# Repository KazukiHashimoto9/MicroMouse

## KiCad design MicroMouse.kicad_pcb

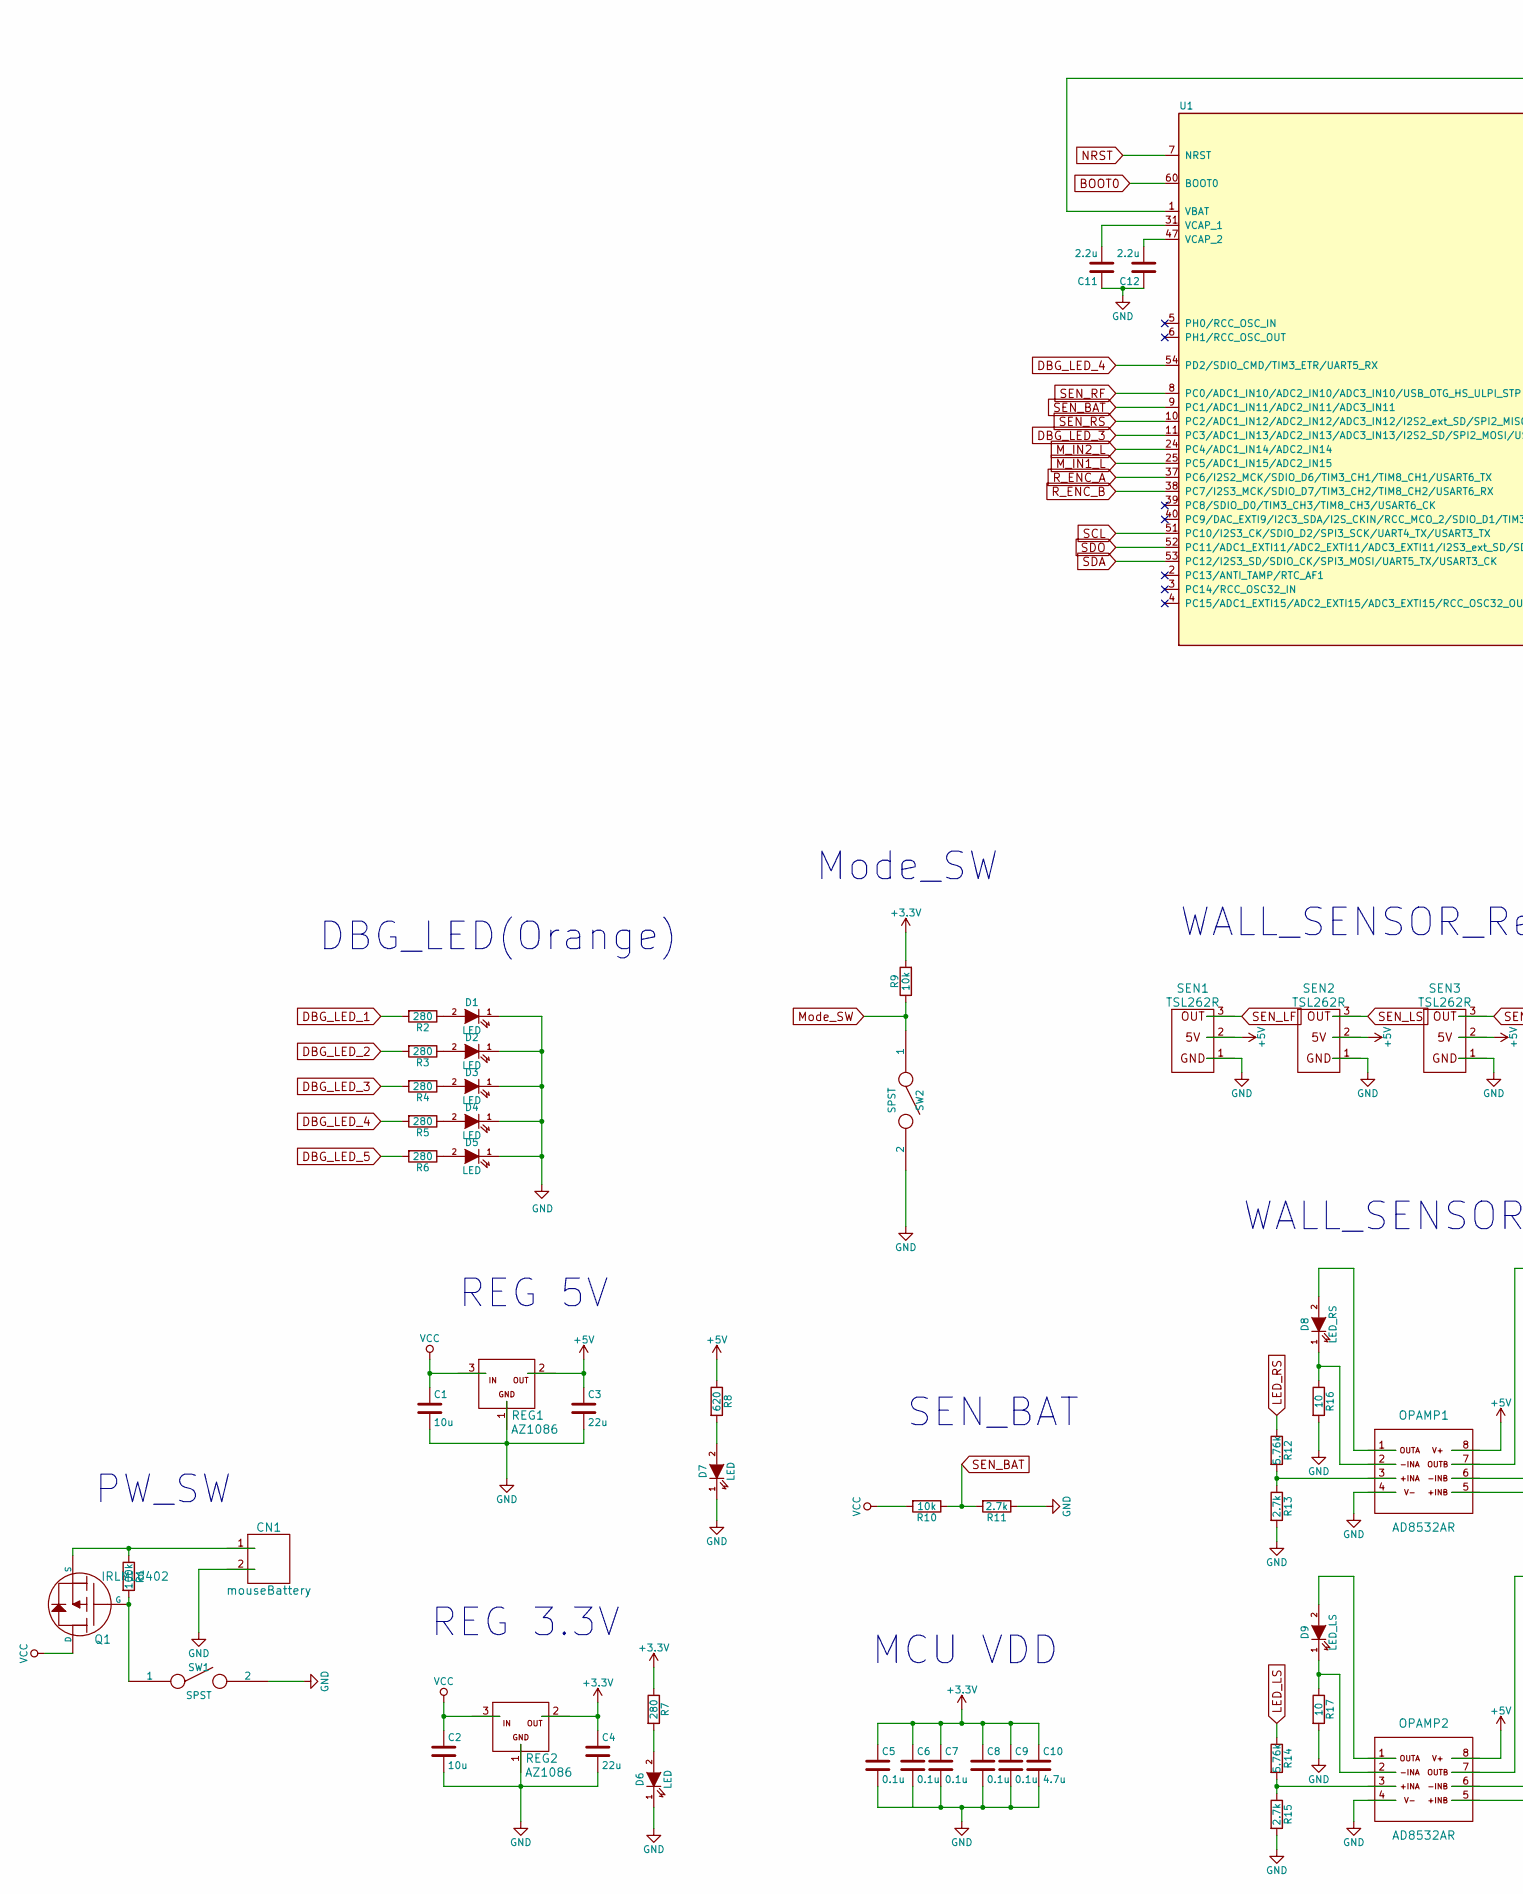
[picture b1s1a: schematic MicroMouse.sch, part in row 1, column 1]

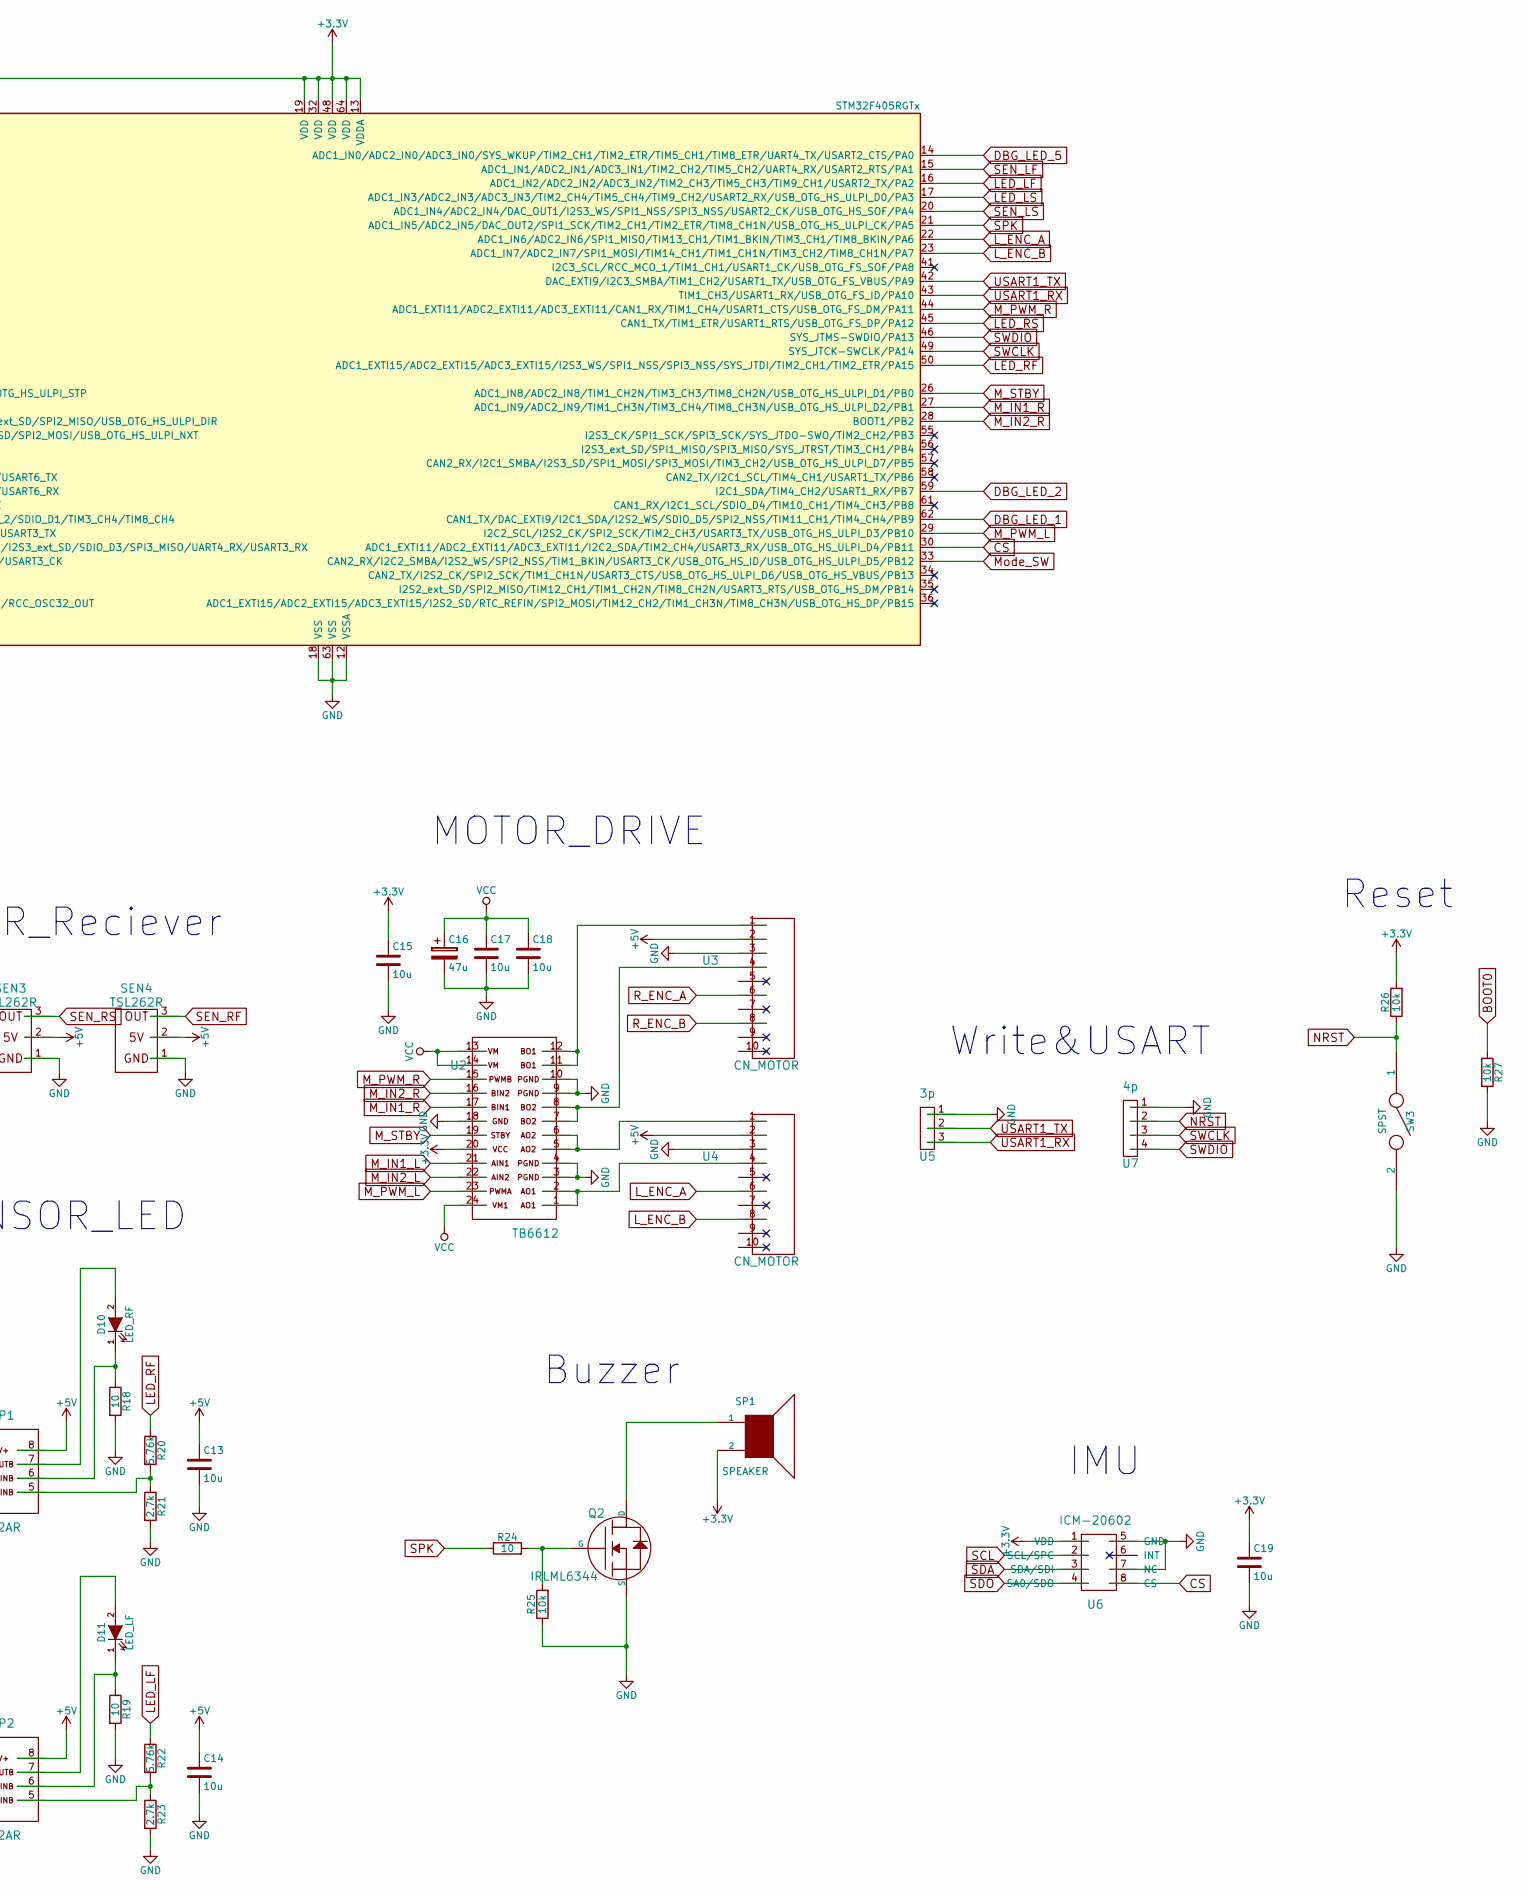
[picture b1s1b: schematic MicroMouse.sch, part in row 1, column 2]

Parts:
C1, C2, C13, C14, C15, C17, C18, C19: 10u; R_0603_HandSoldering
C3, C4: 22u; R_0603_HandSoldering
C5, C6, C7, C8, C9: 0.1u; R_0603_HandSoldering
C10: 4.7u; R_0603_HandSoldering
C11, C12: 2.2u; R_0603_HandSoldering
C16: 47u; c_elec_6.3x7.7
CN1: mouseBattery; XA_2T
D1, D2, D3, D4, D5, D6, D7: LED; R_0603_HandSoldering
D8: LED_RS; LED-5MM
D9: LED_LS; LED-5MM
D10: LED_RF; LED-5MM
D11: LED_LF; LED-5MM
OPAMP1, OPAMP2: AD8532AR; SOIC-8_3.9x4.9mm_Pitch1.27mm
Q1: IRLML6402; SOT-23_Handsoldering
Q2: IRLML6344; SOT-23_Handsoldering
R1: 100k; R_0603_HandSoldering
R2, R3, R4, R5, R6, R7: 280; R_0603_HandSoldering
R8: 620; R_0603_HandSoldering
R9, R10, R25, R26, R27: 10k; R_0603_HandSoldering
R11, R13, R15, R21, R23: 2.7k; R_0603_HandSoldering
R12, R14, R20, R22: 5.76k; R_0603_HandSoldering
R16, R17, R18, R19, R24: 10; R_0603_HandSoldering
REG1, REG2: AZ1086; SOT-223_reg
SEN1, SEN2, SEN3, SEN4: TSL262R; Socket_Strip_Straight_1x03
SP1: SPEAKER; CSS-0575A-SMT
SW1: SPST; SS12D01G4
SW2, SW3: SPST; TVBP06-BN043CB-B
U1: STM32F405RGTx; LQFP-64_10x10mm_Pitch0.5mm
U2: TB6612; SSOP-24_5.3x8.2mm_Pitch0.65mm
U3, U4: CN_MOTOR; BH-10SG
U5: 3p; Pin_Header_Straight_1x03
U6: ICM-20602
U7: 4p; Pin_Header_Straight_1x04

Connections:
+3V3: C4.1, C5.1, C6.1, C7.1, C8.1, C9.1, C10.1, C15.1, C19.1, R7.1, R9.2, R26.2, REG2.2, SP1.2, U1.1 (VBAT), U1.13 (VDDA), U1.19 (VDD), U1.32 (VDD), U1.48 (VDD), U1.64 (VDD), U2.20, U6.1 (VDD); also elsewhere on the board
+5V: C3.1, C13.1, C14.1, OPAMP1.8, OPAMP2.8, R8.1, REG1.2, SEN1.2, SEN2.2, SEN3.2, SEN4.2, U3.2, U4.2; also elsewhere on the board
BOOT0: R27.1, U1.60 (BOOT0)
CS: U1.30 (ADC1_EXTI11/ADC2_EXTI11/ADC3_EXTI11/I2C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), U6.8 (CS)
DBG_LED_1: R2.2, U1.62 (CAN1_TX/DAC_EXTI9/I2C1_SDA/I2S2_WS/SDIO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)
DBG_LED_2: R3.2, U1.59 (I2C1_SDA/TIM4_CH2/USART1_RX/PB7)
DBG_LED_3: R4.2, U1.11 (PC3/ADC1_IN13/ADC2_IN13/ADC3_IN13/I2S2_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)
DBG_LED_4: R5.2, U1.54 (PD2/SDIO_CMD/TIM3_ETR/UART5_RX)
DBG_LED_5: R6.2, U1.14 (ADC1_IN0/ADC2_IN0/ADC3_IN0/SYS_WKUP/TIM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)
GND: C1.2, C2.2, C3.2, C4.2, C5.2, C7.2, C8.2, C9.2, C10.2, C11.1, C12.1, C13.2, C14.2, C15.2, C16.2, C17.2, C18.2, C19.2, CN1.2, D1.1 (K), D2.1 (K), D3.1 (K), D4.1 (K), D5.1 (K), D6.1 (K), D7.1 (K), OPAMP1.4, OPAMP2.4, Q2.2 (S), R11.1, R13.2, R15.2, R16.2, R17.2, R18.2, R19.2, R21.2, R23.2, R25.1, R27.2, REG1.1, REG2.1, SEN1.1, SEN2.1, SEN3.1, SEN4.1, SW1.2, SW2.2, SW3.2, U1.12 (VSSA), U1.18 (VSS), U1.63 (VSS), U2.3, U2.4, U2.9, U2.10, U2.18, U3.3, U4.3, U5.1, U6.5 (GND), U6.7 (NC), U7.1; also elsewhere on the board
LED_LF: R22.1, U1.16 (ADC1_IN2/ADC2_IN2/ADC3_IN2/TIM2_CH3/TIM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)
LED_LS: R14.1, U1.17 (ADC1_IN3/ADC2_IN3/ADC3_IN3/TIM2_CH4/TIM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)
LED_RF: R20.1, U1.50 (ADC1_EXTI15/ADC2_EXTI15/ADC3_EXTI15/I2S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)
LED_RS: R12.1, U1.45 (CAN1_TX/TIM1_ETR/USART1_RTS/USB_OTG_FS_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)
L_ENC_A: U1.22 (ADC1_IN6/ADC2_IN6/SPI1_MISO/TIM13_CH1/T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), U4.6
L_ENC_B: U1.23 (ADC1_IN7/ADC2_IN7/SPI1_MOSI/TIM14_CH1/T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), U4.8
M_IN1_L: U1.25 (PC5/ADC1_IN15/ADC2_IN15), U2.21
M_IN1_R: U1.27 (ADC1_IN9/ADC2_IN9/TIM1_CH3N/TIM3_CH4/TI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), U2.17
M_IN2_L: U1.24 (PC4/ADC1_IN14/ADC2_IN14), U2.22
M_IN2_R: U1.28 (BOOT1/PB2), U2.16
M_PWM_L: U1.29 (I2C2_SCL/I2S2_CK/SPI2_SCK/TIM2_CH3/USAR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), U2.23
M_PWM_R: U1.44 (ADC1_EXTI11/ADC2_EXTI11/ADC3_EXTI11/CAN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), U2.15
M_STBY: U1.26 (ADC1_IN8/ADC2_IN8/TIM1_CH2N/TIM3_CH3/TI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), U2.19
Mode_SW: R9.1, SW2.1, U1.33 (CAN2_RX/I2C2_SMBA/I2S2_WS/SPI2_NSS/TIM1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); also elsewhere on the board
NRST: R26.1, SW3.1, U1.7 (NRST), U7.2; also elsewhere on the board
unnamed: C11.2, U1.31 (VCAP_1)
unnamed: C12.2, U1.47 (VCAP_2)
unnamed: CN1.1, Q1.2 (S), R1.1
unnamed: D1.2 (A), R2.1
unnamed: D2.2 (A), R3.1
unnamed: D3.2 (A), R4.1
unnamed: D4.2 (A), R5.1
unnamed: D5.2 (A), R6.1
unnamed: D6.2 (A), R7.2
unnamed: D7.2 (A), R8.2
unnamed: D8.1 (K), OPAMP1.2, R16.1
unnamed: D8.2 (A), OPAMP1.1
unnamed: D9.1 (K), OPAMP2.2, R17.1
unnamed: D9.2 (A), OPAMP2.1
unnamed: D10.1 (K), OPAMP1.6, R18.1
unnamed: D10.2 (A), OPAMP1.7
unnamed: D11.1 (K), OPAMP2.6, R19.1
unnamed: D11.2 (A), OPAMP2.7
unnamed: OPAMP1.3, R12.2, R13.1
unnamed: OPAMP1.5, R20.2, R21.1
unnamed: OPAMP2.3, R14.2, R15.1
unnamed: OPAMP2.5, R22.2, R23.1
unnamed 47: Q1.1 (G), R1.2, SW1.1; also elsewhere on the board
unnamed: Q2.1 (G), R24.2, R25.2
unnamed 49: Q2.3 (D), SP1.1; also elsewhere on the board
unnamed: U2.1, U2.2, U4.4
unnamed: U2.5, U2.6, U4.1
unnamed: U2.7, U2.8, U3.4
unnamed: U2.11, U2.12, U3.1
R_ENC_A: U1.37 (PC6/I2S2_MCK/SDIO_D6/TIM3_CH1/TIM8_CH1/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), U3.6
R_ENC_B: U1.38 (PC7/I2S3_MCK/SDIO_D7/TIM3_CH2/TIM8_CH2/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), U3.8
SCL: U1.51 (PC10/I2S3_CK/SDIO_D2/SPI3_SCK/UART4_TX/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), U6.2 (SCL/SPC)
SDA: U1.53 (PC12/I2S3_SD/SDIO_CK/SPI3_MOSI/UART5_TX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), U6.3 (SDA/SDI)
SDO: U1.52 (PC11/ADC1_EXTI11/ADC2_EXTI11/ADC3_EXTI1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), U6.4 (SA0/SDO)
SEN_BAT: R10.1, R11.2, U1.9 (PC1/ADC1_IN11/ADC2_IN11/ADC3_IN11)
SEN_LF: SEN1.3, U1.15 (ADC1_IN1/ADC2_IN1/ADC3_IN1/TIM2_CH2/TIM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)
SEN_LS: SEN2.3, U1.20 (ADC1_IN4/ADC2_IN4/DAC_OUT1/I2S3_WS/SPI1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)
SEN_RF: SEN4.3, U1.8 (PC0/ADC1_IN10/ADC2_IN10/ADC3_IN10/USB_O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)
SEN_RS: SEN3.3, U1.10 (PC2/ADC1_IN12/ADC2_IN12/ADC3_IN12/I2S2_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)
SPK: R24.1, U1.21 (ADC1_IN5/ADC2_IN5/DAC_OUT2/SPI1_SCK/TIM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)
SWCLK: U1.49 (SYS_JTCK-SWCLK/PA14), U7.3
SWDIO: U1.46 (SYS_JTMS-SWDIO/PA13), U7.4
USART1_RX: U1.43 (TIM1_CH3/USART1_RX/USB_OTG_FS_ID/PA10), U5.3
USART1_TX: U1.42 (DAC_EXTI9/I2C3_SMBA/TIM1_CH2/USART1_TX/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), U5.2
VCC: C1.1, C2.1, C16.1, C17.1, C18.1, Q1.3 (D), R10.2, REG1.3, REG2.3, U2.13, U2.14, U2.24; also elsewhere on the board

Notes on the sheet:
PW_SW
REG 5V
SEN_BAT
WALL_SENSOR_LED
WALL_SENSOR_Reciever
MOTOR_DRIVE
Buzzer
IMU
REG 3.3V
DBG_LED(Orange)
Write&USART
Reset
Mode_SW
MCU VDD

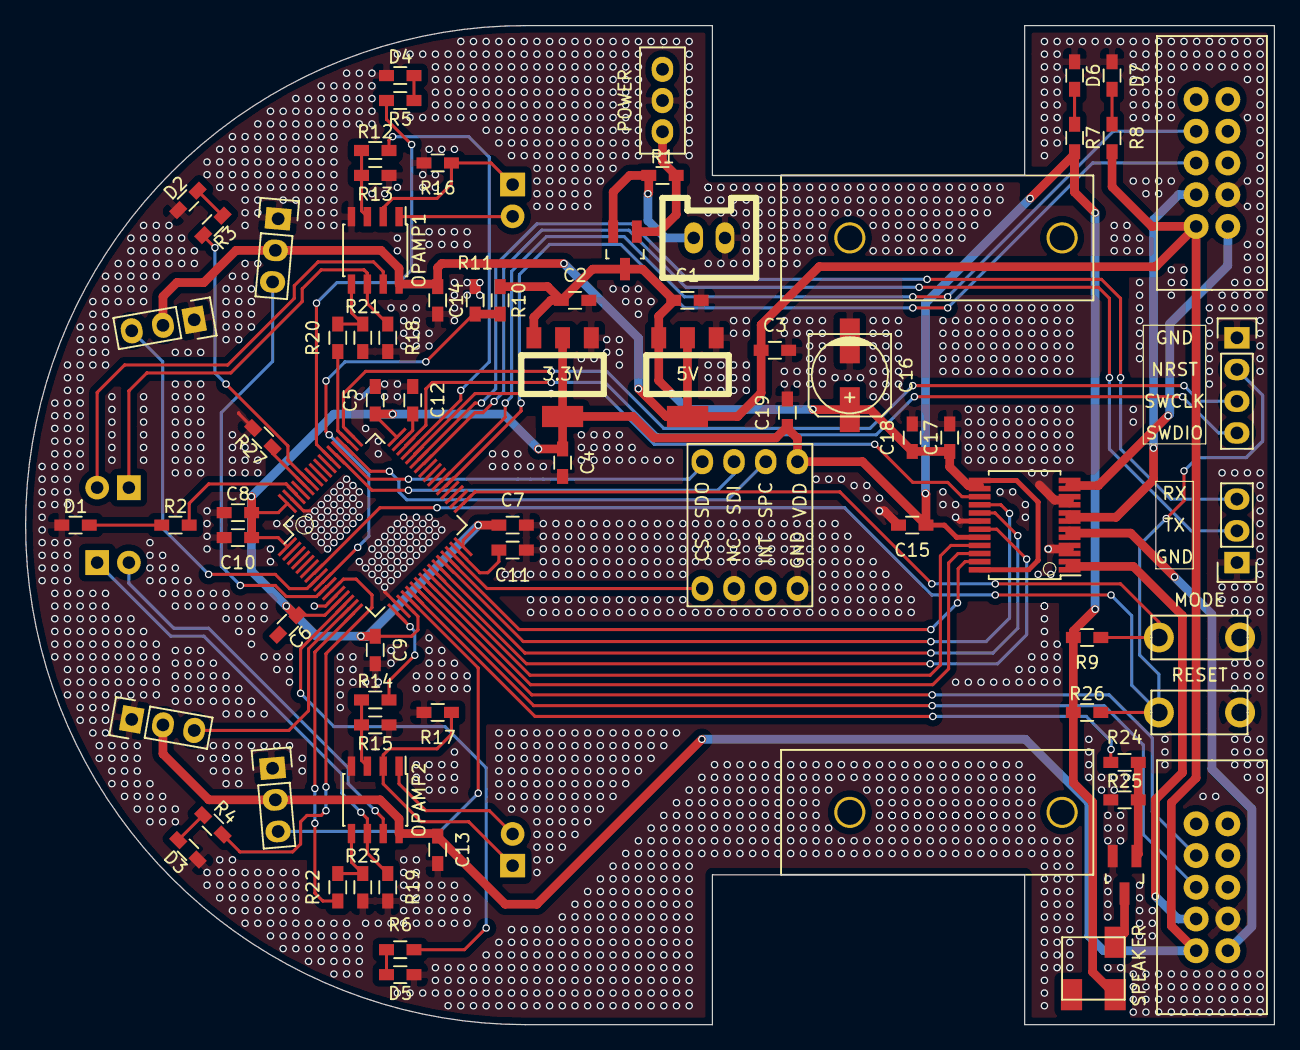
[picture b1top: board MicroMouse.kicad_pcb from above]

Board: 2 copper layers, 100.0 x 80.0 mm, 79 parts (0 on the bottom side), 70 nets.

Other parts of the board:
3.3V, 5V: AZ1086; SOT-223_reg
MODE: SPST; TVBP06-BN043CB-B
POWER: SPST; SS12D01G4
RESET: SPST; TVBP06-BN043CB-B
SPEAKER: SPEAKER; CSS-0575A-SMT

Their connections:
+3V3: 3.3V.2, SPEAKER.2; also elsewhere on the board
+5V: 5V.2; also elsewhere on the board
GND: 3.3V.1, 5V.1, MODE.2, POWER.2, RESET.2; also elsewhere on the board
Mode_SW: MODE.1; also elsewhere on the board
NRST: RESET.1; also elsewhere on the board
unnamed 47: POWER.1; also elsewhere on the board
unnamed 49: SPEAKER.1; also elsewhere on the board
VCC: 3.3V.3, 5V.3; also elsewhere on the board

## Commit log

2018-09-17 修正する前
2019-03-13 変更できるのかのテスト
2019-03-22 とりあえずコミット
2019-05-07 GNDの配線だけした
2019-05-10 向き調整
2019-05-12 昔の確認
2019-05-12 stmのピン変え
2019-05-13 ピン変えました
2019-05-14 pushできるかな
2019-05-15 信号線を引きたいマン
2019-05-16 一応引いた
2019-05-18 GNDベタするマン
2019-05-24 kicadアップデートマン
2019-05-28 led確認
2019-05-30 衝突するやんけ
2019-05-30 電源確認
2019-05-30 ハイパー配線タイム
2019-05-30 信号線を引いていく
2019-05-31 ビア撃ちマン
2019-06-01 GND強化していこうな
2019-06-01 GNDを強化
2019-06-02 あとはビアの調整
2019-06-02 モータマウント取れてた
2019-06-03 ビア打ちまくったマン 最終確認
2019-06-03 とりあえず完成？
2019-06-03 エンコーダ確認
2019-06-04 最終確認
2019-06-04 発注するよ！
2019-06-04 発注した
    何かあったら回路図修正に戻ること
